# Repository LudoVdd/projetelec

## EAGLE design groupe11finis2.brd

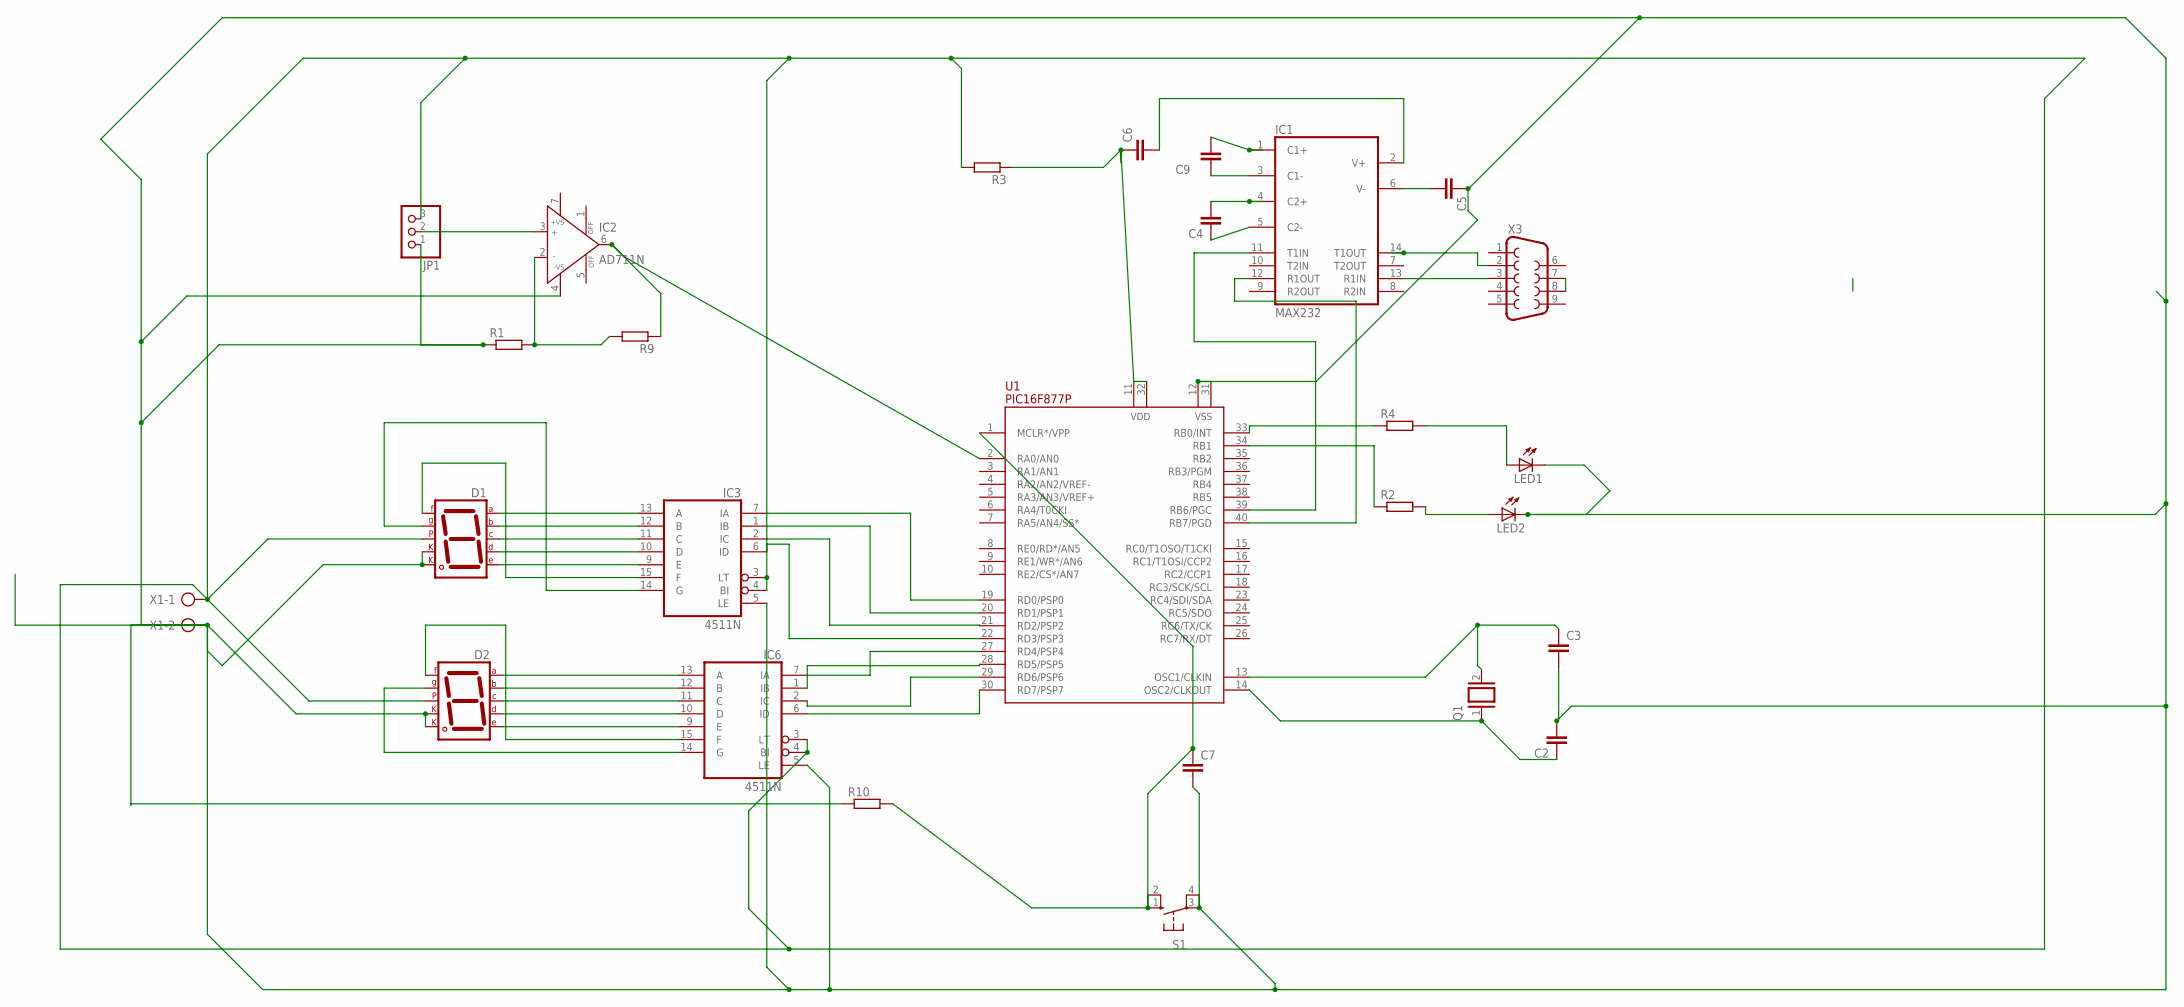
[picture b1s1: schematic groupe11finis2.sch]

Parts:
C2, C3, C4, C5, C6, C7, C9: C-EU025-024X044; C025-024X044
D1, D2: 7SEG-CK; 7SEG-13
IC1: MAX232; DIL16
IC2: AD711N; DIL08
IC3, IC6: 4511N; DIL16
JP1: PINHD-1X3; 1X03
LED1, LED2: LED_ELD260; LED_LD260
Q1: XTAL/S; QS
R1, R2, R3, R4, R9, R10: R-EU_0207/10; 0207/10
S1: 10-XX; B3F-10XX
U1: PIC16F877P; DIL40
X1: AK300/2
X3: F09V

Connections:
GND: IC1.15 (GND)
unnamed: IC1.13 (R1IN), X3.3
unnamed: C9.2, IC1.1 (C1+)
unnamed: IC1.14 (T1OUT), X3.2
unnamed: C9.1, IC1.3 (C1-)
unnamed: IC1.11 (T1IN), U1.39 (RB6/PGC)
unnamed: C4.2, IC1.4 (C2+)
unnamed: IC1.12 (R1OUT), U1.40 (RB7/PGD)
unnamed: C4.1, IC1.5 (C2-)
unnamed: C6.2, IC1.2 (V+)
unnamed: C5.2, IC1.6 (V-)
unnamed: IC3.7 (IA), U1.19 (RD0/PSP0)
unnamed: IC3.1 (IB), U1.20 (RD1/PSP1)
unnamed: IC3.2 (IC), U1.21 (RD2/PSP2)
unnamed: IC3.6 (ID), U1.22 (RD3/PSP3)
unnamed: IC6.7 (IA), U1.27 (RD4/PSP4)
unnamed: IC6.1 (IB), U1.28 (RD5/PSP5)
unnamed: IC6.2 (IC), U1.29 (RD6/PSP6)
unnamed: IC6.6 (ID), U1.30 (RD7/PSP7)
unnamed: D1.7 (A), IC3.13 (A)
unnamed: D1.6 (B), IC3.12 (B)
unnamed: D1.4 (C), IC3.11 (C)
unnamed: D1.2 (D), IC3.10 (D)
unnamed: D1.1 (E), IC3.9 (E)
unnamed: D1.9 (F), IC3.15 (F)
unnamed: D1.10 (G), IC3.14 (G)
unnamed: D2.7 (A), IC6.13 (A)
unnamed: LED2.A, R2.2
unnamed: D2.6 (B), IC6.12 (B)
unnamed: R2.1, U1.34 (RB1)
unnamed: D2.2 (D), IC6.10 (D)
unnamed: D2.1 (E), IC6.9 (E)
unnamed: D2.9 (F), IC6.15 (F)
unnamed: D2.10 (G), IC6.14 (G)
unnamed: R4.1, U1.33 (RB0/INT)
unnamed: IC2.3 (IN+), JP1.2
unnamed: LED1.A, R4.2
unnamed: IC2.2 (IN-), R1.2, R9.2
unnamed: C3.1, Q1.2, U1.13 (OSC1/CLKIN)
unnamed: C7.1, R10.2, S1.1 (S), S1.2 (S1), U1.1 (MCLR*/VPP)
unnamed: C2.1, Q1.1, U1.14 (OSC2/CLKOUT)
unnamed: X3.7, X3.8
unnamed: IC2.6 (OUT), R9.1, U1.2 (RA0/AN0)
unnamed: C6.1, R3.1, U1.11 (VDD), U1.32 (VDD)
unnamed: D2.4 (C), IC6.11 (C)
unnamed: D1.5 (DP), D2.5 (DP), IC3.3 (LT), IC3.4 (BI), IC6.3 (LT), IC6.4 (BI), JP1.3, R3.2, X1.1
unnamed: C2.2, C3.2, C5.1, C7.2, D1.3 (CK1), D1.8 (CK2), D2.3 (CK1), D2.8 (CK2), IC2.4 (-VS), IC3.5 (LE), IC6.5 (LE), JP1.1, LED1.K (C), LED2.K (C), R1.1, R10.1, S1.3, S1.4 (P1), U1.12 (VSS), U1.31 (VSS), X1.2
VCC: IC1.16 (VCC)
VDD: IC3.16 (VDD), IC6.16 (VDD)
VSS: IC3.8 (VSS), IC6.8 (VSS)

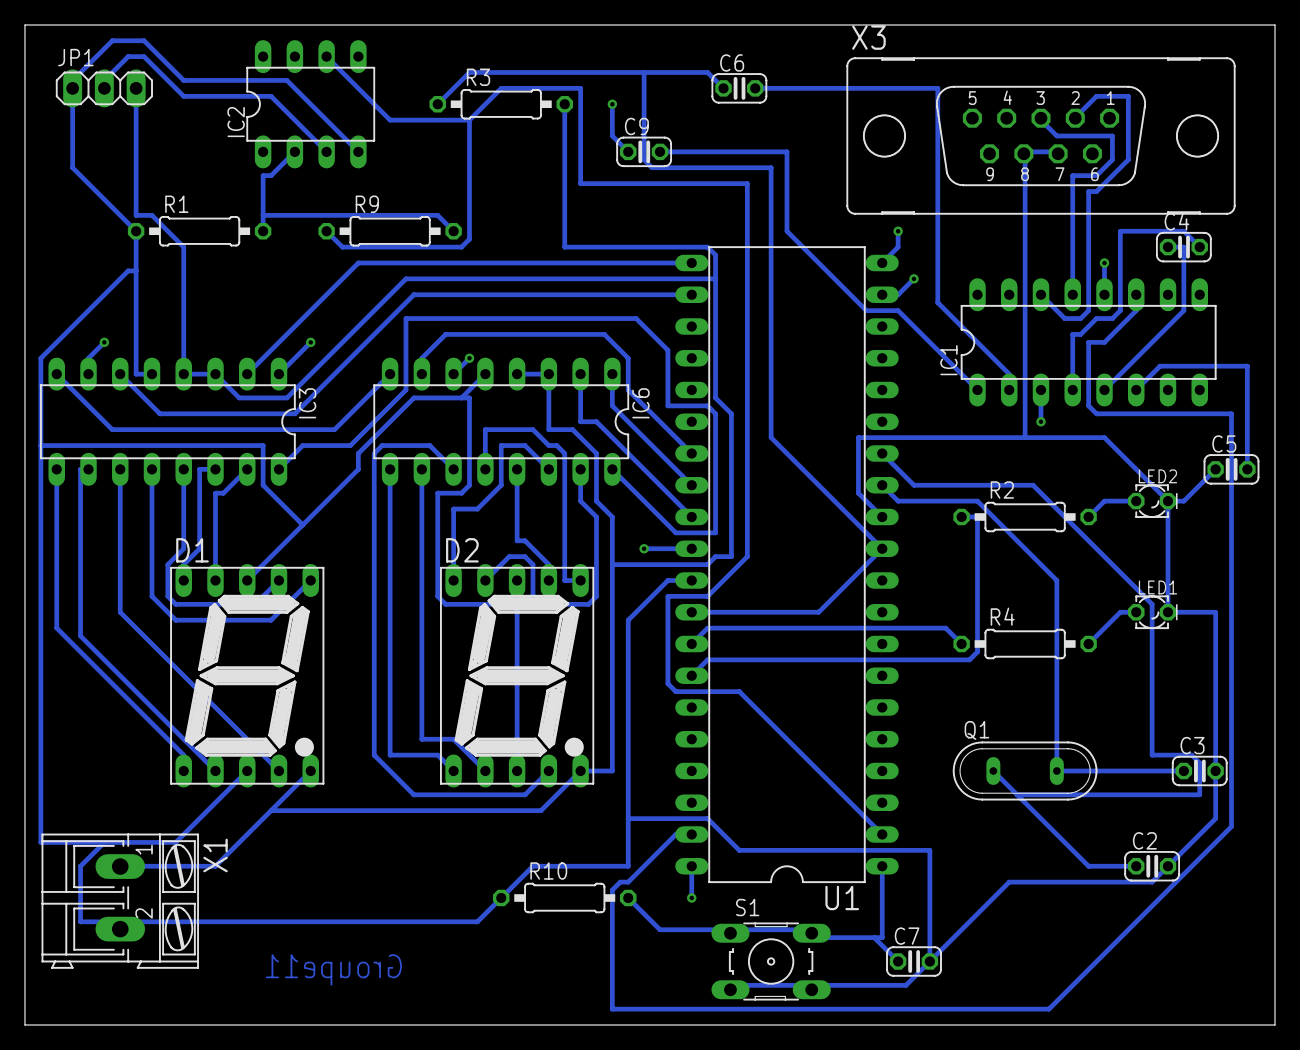
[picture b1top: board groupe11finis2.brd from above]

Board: 2 copper layers, 100.0 x 80.0 mm, 27 parts (0 on the bottom side), 48 nets.

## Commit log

2019-05-20 Create Proteus
2019-05-20 Create schémas
2019-05-20 Create Protéus
2019-05-20 Create test
